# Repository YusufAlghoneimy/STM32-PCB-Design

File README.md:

# STM32-PCB-Design

# STM32F103C8T6 Development Board (KiCad)

A custom 2 Layer STM32 development board designed in **KiCad 9** as a learning project. This PCB is based on the **STM32F103C8T6** microcontroller and includes the essential hardware required for programming, debugging, USB communication, and external peripheral interfacing.

Reference:
Datasheet used: (https://octopart.com/part/stmicroelectronics/STM32F103C8T6?gad_source=1&gad_campaignid=20642695372&gbraid=0AAAAADZKcp-Alkbb7IeYK6pH4JAVgc0-K&gclid=Cj0KCQjwxvjRBhC2ARIsAI7KJa20-8JRL5y0QMiAJF_y9Jzo9iUv5DF9WO-H_aE_pG1OXbHMajoYCr0aAm-cEALw_wcB)

Youtube PCB design reference: Phil's Lab (https://www.youtube.com/watch?v=nkHFoxe0mrU&pp=ygUMa2ljYWRrIHN0bTMy) & (https://www.youtube.com/watch?v=aVUqaB0IMh4&t=234s)

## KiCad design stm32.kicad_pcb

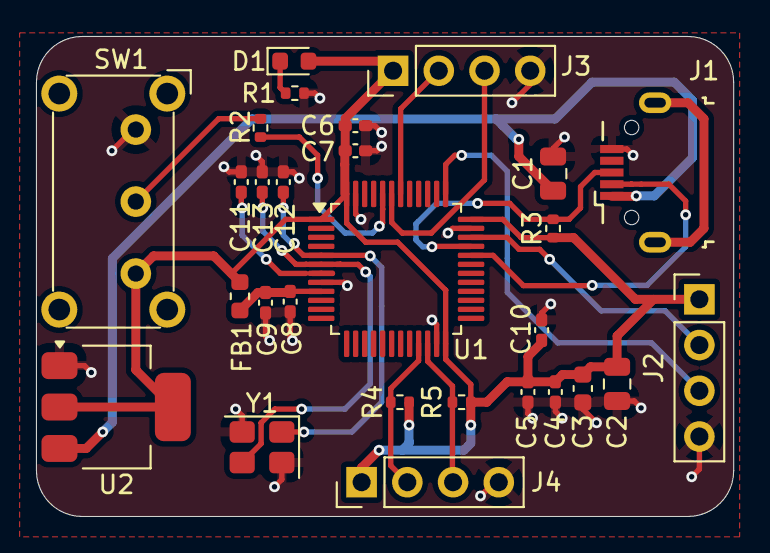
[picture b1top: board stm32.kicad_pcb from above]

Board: 2 copper layers, 38.7 x 26.7 mm, 28 parts (0 on the bottom side), 18 nets.

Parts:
C1, C2: 22u; C_0805_2012Metric
C3: 10u; C_0603_1608Metric
C4, C5, C6, C7, C11: 100n; C_0402_1005Metric_Pad0.74x0.62mm_HandSolder
C8: 10n; C_0402_1005Metric_Pad0.74x0.62mm_HandSolder
C9, C10: 1u; C_0402_1005Metric_Pad0.74x0.62mm_HandSolder
C12, C13: 10p; C_0402_1005Metric_Pad0.74x0.62mm_HandSolder
D1: LED; LED_0603_1608Metric
FB1: 120R; L_0603_1608Metric
J1: USB_B_Micro; USB_Micro-B_Wuerth_629105150521
J2, J3, J4: Conn_01x04_Pin; PinHeader_1x04_P2.54mm_Vertical
R1, R3, R4, R5: 1k5; R_0402_1005Metric
R2: 10K; R_0402_1005Metric
SW1: SW_SPDT; SW_E-Switch_EG1224_SPDT_Angled
U1: STM32F103C8T6; LQFP-48_7x7mm_P0.5mm
U2: AMS1117-3.3; SOT-223-3_TabPin2
Y1: 16MHz; Crystal_SMD_3225-4Pin_3.2x2.5mm

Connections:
+3.3V: C2.1, C3.1, C4.1, C5.1, C6.1, C7.1, C10.1, D1.2 (A), FB1.2, J2.1, J3.1, J4.1, R3.1, R4.1, R5.1, SW1.3 (C), U1.1 (VBAT), U1.24 (VDD), U1.36 (VDD), U1.48 (VDD), U2.2 (VO)
+3.3VA: C8.1, C9.1, FB1.1, U1.9 (VDDA)
/BOOT0: R2.2, U1.44 (BOOT0)
/HSE_IN: C12.1, U1.5 (PD0), Y1.1
/HSE_OUT: C13.1, U1.6 (PD1), Y1.3
/I2C2_SCL: J4.2, R4.2, U1.21 (PB10)
/I2C2_SDA: J4.3, R5.2, U1.22 (PB11)
/NRST: C11.1, U1.7 (NRST)
/POWER_LED_K: D1.1 (K), R1.1
/SWCLK: J2.3, U1.37 (PA14)
/SWDIO: J2.2, U1.34 (PA13)
/SW_BOOT0: R2.1, SW1.2 (B)
/USART1_RX: J3.3, U1.43 (PB7)
/USART1_TX: J3.2, U1.42 (PB6)
/USB_D+: J1.3 (D+), R3.2, U1.33 (PA12)
/USB_D-: J1.2 (D-), U1.32 (PA11)
GND: C1.2, C2.2, C3.2, C4.2, C5.2, C6.2, C7.2, C8.2, C9.2, C10.2, C11.2, C12.2, C13.2, J1.5 (GND), J2.4, J3.4, J4.4, R1.2, SW1.1 (A), U1.8 (VSSA), U1.23 (VSS), U1.35 (VSS), U1.47 (VSS), U2.1 (GND), Y1.2 (G), Y1.4 (G)
VBUS: C1.1, J1.1 (VBUS), U2.3 (VI)
